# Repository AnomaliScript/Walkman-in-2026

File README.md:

# Walkman-in-2026
As a part of Hack Club's "Fallout" challenge, I attempt to build a replica of Makoto's walkman (from Persona 3) using KiCad, Onshape, and hopes and dreams.

This Walkman composes of many capacitors, resistors, an Audio Jack, a microSD card socket, LCD display, four buttons, an on/off switch, and most importantly, a XIAO-ESP3-S3 to make it all work!
Most, if not all of these components are THT, or "through-hole technology", meaning that the components have pins that go through holes in the PCB, making them easier to soldier, and that's why I chose THT components (with the exceptino of the microSD card reader), because I'm not a soldering expert (yet).

## V0.1
I made my own custom "standoffs" which are supports that support the LCD display, because it needs extra vertical room in order for its pins to be connected to the PCB.  I 3D printed both a "screw" and a "non-screw" version of the standoffs, to test which one would work best (standoffs are small, and the smaller a print is, the worse small details, like screw patterns, will be).

The screw standoff's didn't work, becasue my 3D printer can't print with that amount of sub-millimeter precision, so I'll just have to use the "non-screw" version of the standoffs.

## V0.2
The biggest change from V0.1 was the addition of an Amazon-purchased breakout board that covered both the AudioJack (3.5mm diameter) and PCM5102A stereo.  After all, the PCM5102A is indeed a really tiny chip, and with the soldering iron that I was getting, it wasn't likely that I could've soldered the chip using SMD (surface mount) on my own.  Consequently, I had to rewire the whole PCB (this will happen many times...) to compensate for this change.
What I specifically did was delete the AudioJack and PCM components from the PCB, and put a 16-pin connetor row in its place to set it up for wires to connect to the breakout module (a decision I would later go back on).
I also cleaned up the BOM a little bit, but it still was missing a lot of components compared to the final one (which I will link in the bottom of this README).

I was planning to get many of my components from my school's makerspace, however since Georgia school years end in mid-May, I lost access to those spaces, and therefore couldn't access those resources: this meant that I had to go shop online (i.e. Amazon and Digikey).
V0.2 was also when I finally started to consider how to power this whole contraption, and the conclusion I came up with was simply to add some punches holes (called  "Jumper" in the KiCad schematic) to have the battery wires solder through.

## V0.3
The buttons on the Walkman PCB looks a bit off; maybe it's because they're not tilted 90 degrees!  While implementing right-angle switches, I learned about the different types of drill holes that KiCad offers (I had the wrong type of hole for the switches' footprints which was giving me DRC errors).

This was also when I became very insecure about my power management system, so this was when I learned that the XIAO-ESP3-S3 in fact has a built-in nattery management system that rules out the need for Buck converters and other auxillary power managemtn components, which was a huge relief after having done power research for a couple of days straight.  The only problem was how to get the power tracks/wires to connect to the bottom of the XIAO, becasue that's where the XIAO's battery pads (BATT) are.  Seeing as to how laying the XIAO against teh PCB would make it impossible for a wire to reach under the XIAO, I decided to elevate it using connectors (not shown in the KiCad 3D Viewer below).

## V0.4
I went back on my decision to physically elevate my XIAO from the PCB.
After a family vacation, my refreshed mind preferred to create pads on the XIAO footprint itself.  By adding the BATT pads onto the footprint itself, the XIAO, when it comes in contact with the PCB direcly, would have its BATT pads touch the PCB's corresponding pads, requiring no extraneous equiment to connect the two.
This customization of the orignal XIAO-ESP32-S3 footprint required me to refer to Seeed Studio's offical KiCad files in order to determine the dimensions and position of the BATT pads, becasue the XIAOs that I ordered were still in transit at the time, so I had no other reference.

The XIAO BATT pads and its PCB footprint counterpart, in theory, seemed to perfectly align with each other.

I also learned that I had ordered the wrong type of switch for the power, as I ordered a SW_SPST (a button) instead of a SW_DPST (an actual power switch that toggles), so I had to order SW_DPST switches.
The LCD that I got was also an unexpected (but plesant) surprise: it came with the PCF8574 component (a component that allows for more GPIO pins) already soldered onto the LCD1602.  After realizing that this aligned with my PCB schematic, I gladly deleted the PCF8574 from my schematic and PCB Editor, and more configuration was done.

Due to the unique pin that the LCD came with, however, I had to redo the footprint for the LCD as well.

## V0.5
Reviewing my the PCB, I realized that the 5V pin on the LCD wasn't connected to anything, and thus began the **third** reexamination of my PCB's power management.  After scrutiny, I fixed the 5V pin on the LCD fairly quickly (connect the 5V on the LCD to the VBUS pin on the XIAO), but there was another issue that I found, and it had to do with the BSS138 components.  BSS138s are what are called "bidirectional I2C level shifters", which means they mediate the translation between a higher voltage (e.g. 5V) and a lower voltage (3V).  Cleaning up my schematic to mitigate risks of making errors due to confusion, I then revised the BSS connections.

Once again, I had to rewire everything (BSS138 is a surface-mount/SMD component, which made rerouting a little harder).

I also noticed that I really needed a 3D model for the LCD component, becasue that was not only the biggest part, but it's also one of the most important parts when it came to me designing a housing/case for my PCB.  Surfing through the internet, I landed upon a sketchy-looking 3D model of the exact same component (I copied and pasted the Amazon name of the component into Google), and it was in some Autodesk-specific file format.  After registering for a free trial for Autodesk products (specifically Fusion 360), I converted into an .stl file and imported into OnShape to look at it further.  The model  wasn't that bad, and when I linked the 3D model to my LCD footprint on the PCB in KiCad, it fit right in!
One tiny change had to be made, and it was the deletion of the right-angle pins (I bent the pins on my LCD to make it straight to make it parallel to the PCB surface...I hope that doesn't mess up dimensioning...)

## V1.0
Remember the 16-pin connector that I mentioned?  Their job was to act as pins that wires from the AudioJack breakout module could connect to, but seeing as to how it adds unnecessary space to the Walkman, I designed the AudioJack component as a footprint in the PCB Editor to get rid of the 16-pin connector (this did in fact save a lot of space).  This required some dimensioning, which I did, and I made a rough OnShape model of it.  Exporting it onto the 3D Viewer in my PCB Editor on KiCad, I moved it up a bit (which will represent me using pinn connectors to elevate it) in order to give it some room so it doesn't collide with the right-angle switches.

I utilized my 3D printer to print simplified versions of my PCB to check the footprints and pin dimensions for the XIAO, LCD component, and AudioJack component (not pictured), but after verification I ordered the PCB from JLCPCB, and now I wait for it to come (as well as some other LCSC components).

# BOM (not including delivery fees + tariffs)
| Id      | Name    | Vendor  | Qty     | Cost |
| --- | --- | --- | --- | --- |
| 1 | [microSD card slot](https://www.digikey.com/en/products/detail/molex/0472192001/3044807) | DigiKey | 10 | $14 |
| 2 | [BSS138](https://www.digikey.com/en/products/detail/onsemi/BSS138/244210)| DigiKey | 10 | $2 |
| 3 | [Power Switch (taken from my friend's recommendation)](https://www.lcsc.com/product-detail/Slide-Switches_C-K-OS102011MA1QN1_C226259.html) | LCSC | 10 | $5.25 |
| 4 | [XIAO ESP32S3](https://www.amazon.com/ESP32S3-2-4GHz-Dual-core-Supported-Efficiency-Interface/dp/B0DJ6NQFKX/ref=pd_rhf_dp_s_ci_mcx_mr__d_sccl_1_1/137-7709202-3397348) | Amazon | 3 | $27 |
| 5 | [1602 LCD + PCF 8524 module](https://www.amazon.com/Hosyond-Display-Module-Arduino-Raspberry/dp/B0BWTFN9WF/ref=pd_rhf_dp_s_ci_mcx_mr__d_sccl_1_3/137-7709202-3397348) | Amazon | 3 | $14 |
| 6 | [AudioJack + PCM 5102 module](https://www.amazon.com/PCM5102-PCM5102A-Digital-Converter-Raspberry/dp/B0DNW32Y46/ref=sims_dp_d_dex_ai_rank_model_1_d_v1_d_sccl_1_3/137-7709202-3397348?psc=1) | Amazon | 2 | $9 |
| 7 | [1000mAh LiPo battery](https://www.amazon.com/1000mAh-battery-Rechargeable-Lithium-Connector/dp/B07BTWK13N) | Amazon | 1 | $9 |
| 8 | [Right-Angle Switches](https://www.lcsc.com/product-detail/C49101620.html?spm=wm.ddx.0.xqy___wm.ddl.ddb.0.ddh&lcsc_vid=ElUPAwcDQFlaVF0HQ1dXAwFXFVNbUVFeQFIPBQIHQgQxVlNeR1FZVVVQR1laVTsOAxUeFF5JWBYZEEoKFBINSQcJGk4NBhADEA4cHktSR1RADxALGw%3D%3D) | LCSC | 50 | $0.63 |
| X | X | X | X | ~$81 |

## Additional supplies

I started to get soldering supplies by asking my friend's dad for some, to which he responded with a simple roll of solder and an okay soldering iron.  This worked out fine for the simpler components, but when it came to more complex soldering assemblies such as SMD components, I needed help.
After some discussion with by more-experienced friend, he told me that I needed a pack of liquid/solid flux (just in case if the rosin-core solder didn't have enough), a heatbed for the SMD components, and some solder paste to complement the heatbed for easier soldering for SMD components.
| Id      | Name    | Vendor  | Qty     | Cost |
| --- | --- | --- | --- | --- |
| 1 | [Heatbed](https://www.amazon.com/Soldering-Microcomputer-Technicians-Electronics-Enthusiasts/dp/B0G443BG4X/ref=sr_1_2?sr=8-2) | Amazon | 1 | $27 |
| 2 | [Flux](https://www.amazon.com/SRA-Soldering-Electronics-Lead-Free-Electrical/dp/B008ZIV85A/ref=sr_1_6?crid=3PSC9N7K6VI1P&dib=eyJ2IjoiMSJ9.4lAJRvPbs-mZfOjdNN3yko1QdCRJ7DuF7ITQXP00Zw6-YTXEtz6O56z-3mFeA06DFWn7K46TQMWEEocoB24hUeA2pRWL5PZLodoffU67bT22aAduVxkx_wdd-4mv4hNAZPr-tqz4AYCK0zWmtre61fzN7fRagjiYjk4f0m6PkqVZ_U-DropUBjAUAZUFRuWYf_Zg6Ls1t9Iee1CwaPx7wRCERDrgLYxmO5XsuhNiYI31TFE8GYnA0AEQibicbohzDRZsgtbbjuhwPmBq9184HANk6QaEDnCSlJgSGyVij_4.RXMTRwdvJQXcmnfBtIILk3Vw2HaX5XoBBaaOHqvCQDs&dib_tag=se&keywords=solder+flux&qid=1787439264&sprefix=solder+flu%2Caps%2C151&sr=8-6) | Amazon | 1 | $9 |
| 3 | [Solder Paste](https://www.amazon.com/Particle-Melting-Electronics-Welding-100G/dp/B0FYH9HS2W/ref=sr_1_24?crid=1XXM8RE6MJU3V&dib=eyJ2IjoiMSJ9.RM36QPd0a2H4_bdhGSOKfZJjHoW4TT7FYbYOePXYuUSKFAHb8I43R-8Ku84GS6KqnE81AwtSetvDehl8jUrOpetkE9Lp1e0oAUrra1Ax1yHaP54gxSOjCNy8Qae3zJZ3lqb1vRmu-jv4T_6l-unRR69yQe7E2hoBbOXNDQxANlSyCc-yngeB1UcluzowntyGix_HBKZ0-sbckXMkqIkEe25zazsldICJT3-jejK2Nnjor7P6o3duiNHdLID88EolUzPUfiM_pN3laRQF3XeSDC66AEbr2nc3RMiYHQiKlFM.QaV3XLYiIFU6J7uR8jqXOCL1FU7gVYKlh0sjLuVEvP0&dib_tag=se&keywords=solder+paste&qid=1787439314&sprefix=solder+pas%2Caps%2C222&sr=8-24) | Amazon | 1 | $22 |

After getting these components, I set up shop in my garage, and I opened the garage door so that the yummy lead fumes could escape.  However, I got moved to my back patio after my dad complained after a bunch of bugs came it in from the open garage door.

Finally, after having done most of the soldering to enable theoretical functionality for my Walkman, I tried hooking it up to my computer using a Logi USB-C cable, and after some vibecoding with Claude Opus, I got the Walkman to work...partially.  The display was a little off, and no matter how many times I unplugged and replugged my earbuds, I still couldn't hear anything from the Walkman.  Thankfully, the microSD card reader was working, as well as the LCD after some adjustment, because I saw it displaying the text of the songs that I had loaded onto the microSD card.

Switching out my earbuds for headphones that I usually use, I was finally able to hear the music that was playing!

However, the battery still needed to be implemented into the Walkman PCB, and I soon realized that the V1.0 Walkman PCB wouldn't be able to distribute the LiPo battery's power to all the peripherals on the PCB.  This was because I wired the AudioJack, LCD display, and all the other peripherals other than the microSD card to all use VBUS (5V) power instead of 3.3V power.  The problem lied in how the 3.3V pin, not the VBUS pin, was the only power distributor when the Walkman is disconnected from the XIAO's USB-C's power source.

## V2.0 
With the LiPo power distribution not working and the LCD screen not being entirely accurate to Makoto's Walkman in Persona 3, I returned to the drawing board that is KiCad.  By working with Claude, I found another [LCD screen](https://newhavendisplay.com/2x20-character-lcd-stn-gray-display-with-side-white-backlight-and-pin-header-3v/) online that looked more similar to Makoto's Walkman screen.  Looking at its datasheet, I tried adding it into my Walkman PCB schematic.

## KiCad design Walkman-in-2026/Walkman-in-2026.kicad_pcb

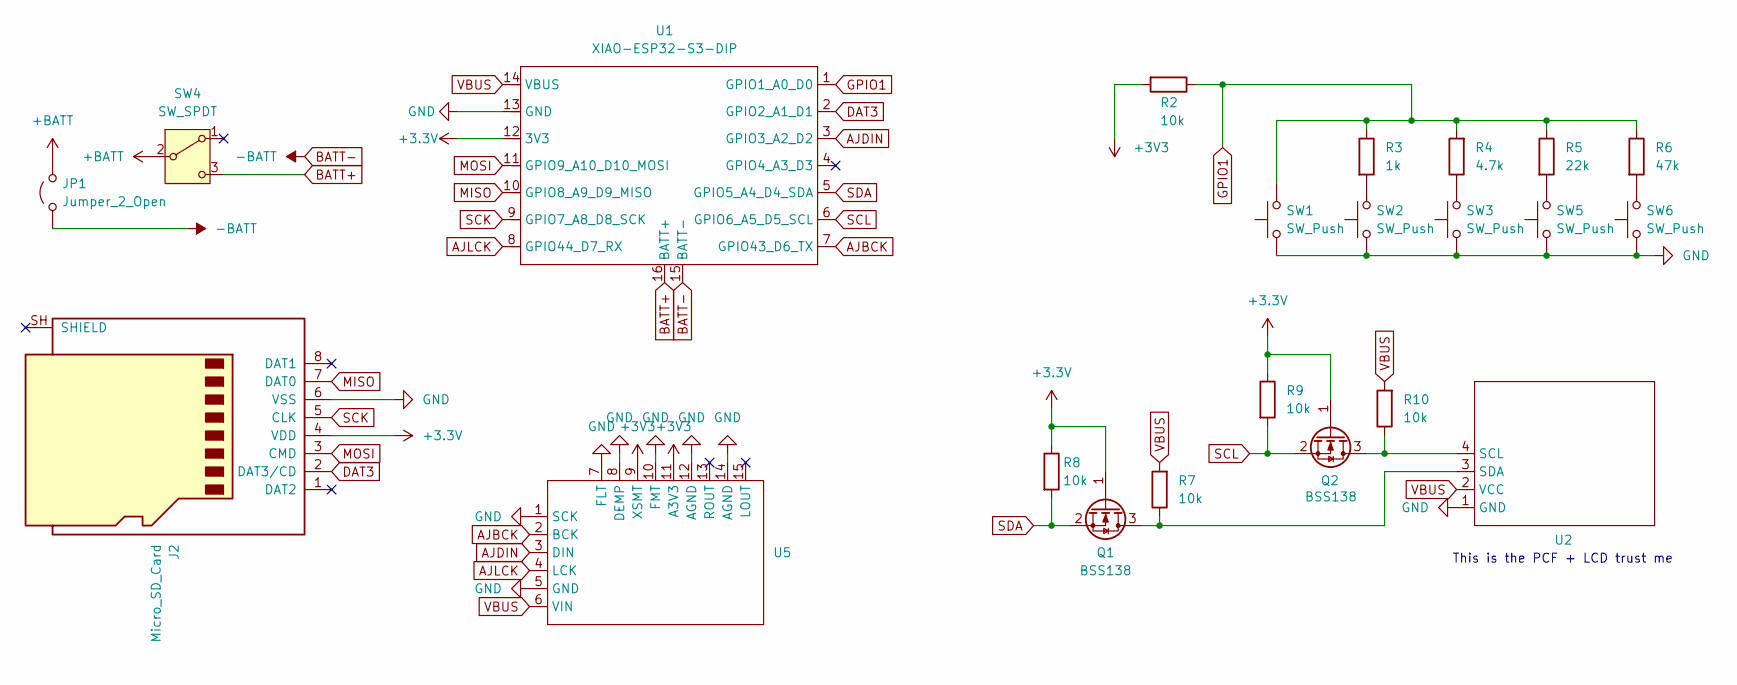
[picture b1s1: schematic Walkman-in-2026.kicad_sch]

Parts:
J2: Micro_SD_Card; microSD_HC_Molex_47219-2001
JP1: Jumper_2_Open; TestPoint_2Pads_Pitch2.54mm_Drill0.8mm
Q1, Q2: BSS138; SOT-23
R2, R7, R8, R9, R10: 10k; R_Axial_DIN0207_L6.3mm_D2.5mm_P7.62mm_Horizontal
R3: 1k; R_Axial_DIN0207_L6.3mm_D2.5mm_P7.62mm_Horizontal
R4: 4.7k; R_Axial_DIN0207_L6.3mm_D2.5mm_P7.62mm_Horizontal
R5: 22k; R_Axial_DIN0207_L6.3mm_D2.5mm_P7.62mm_Horizontal
R6: 47k; R_Axial_DIN0207_L6.3mm_D2.5mm_P7.62mm_Horizontal
SW1, SW2, SW3, SW5, SW6: SW_Push; SW-SMD_TC-S3601-3.5-260G-F0.6
SW4: SW_SPDT; SW_Slide_SPDT_Angled_CK_OS102011MA1Q
U1: XIAO-ESP32-S3-DIP
U2: PCF8574 x LCD1602 combo
U5: PCM x AudioJack Combo

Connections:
+3.3V: J2.4 (VDD), Q1.1 (G), Q2.1 (G), R8.1, R9.1, U1.12 (3V3)
+3V3: R2.2, U5.9 (XSMT), U5.11 (A3V3)
+BATT: JP1.2 (B), SW4.2 (B)
AJBCK: U1.7 (GPIO43_D6_TX), U5.2 (BCK)
AJDIN: U1.3 (GPIO3_A2_D2), U5.3 (DIN)
AJLCK: U1.8 (GPIO44_D7_RX), U5.4 (LCK)
BATT+: SW4.3 (C), U1.16 (BATT+)
BATT-: JP1.1 (A), U1.15 (BATT-)
DAT3: J2.2 (DAT3/CD), U1.2 (GPIO2_A1_D1)
GND: J2.6 (VSS), SW1.1, SW2.1, SW3.1, SW5.1, SW6.1, U1.13 (GND), U2.1 (GND), U5.1 (SCK), U5.5 (GND), U5.7 (FLT), U5.8 (DEMP), U5.10 (FMT), U5.12 (AGND), U5.14 (AGND)
GPIO1: R2.1, R3.1, R4.2, R5.1, R6.1, SW1.2, U1.1 (GPIO1_A0_D0)
MISO: J2.7 (DAT0), U1.10 (GPIO8_A9_D9_MISO)
MOSI: J2.3 (CMD), U1.11 (GPIO9_A10_D10_MOSI)
unnamed: Q1.3 (D), R7.1, U2.3 (SDA)
unnamed: Q2.3 (D), R10.1, U2.4 (SCL)
unnamed: R3.2, SW2.2
unnamed: R4.1, SW3.2
unnamed: R5.2, SW5.2
unnamed: R6.2, SW6.2
SCK: J2.5 (CLK), U1.9 (GPIO7_A8_D8_SCK)
SCL: Q2.2 (S), R9.2, U1.6 (GPIO6_A5_D5_SCL)
SDA: Q1.2 (S), R8.2, U1.5 (GPIO5_A4_D4_SDA)
VBUS: R7.2, R10.2, U1.14 (VBUS), U2.2 (VCC), U5.6 (VIN)

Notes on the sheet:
This is the PCF + LCD trust me

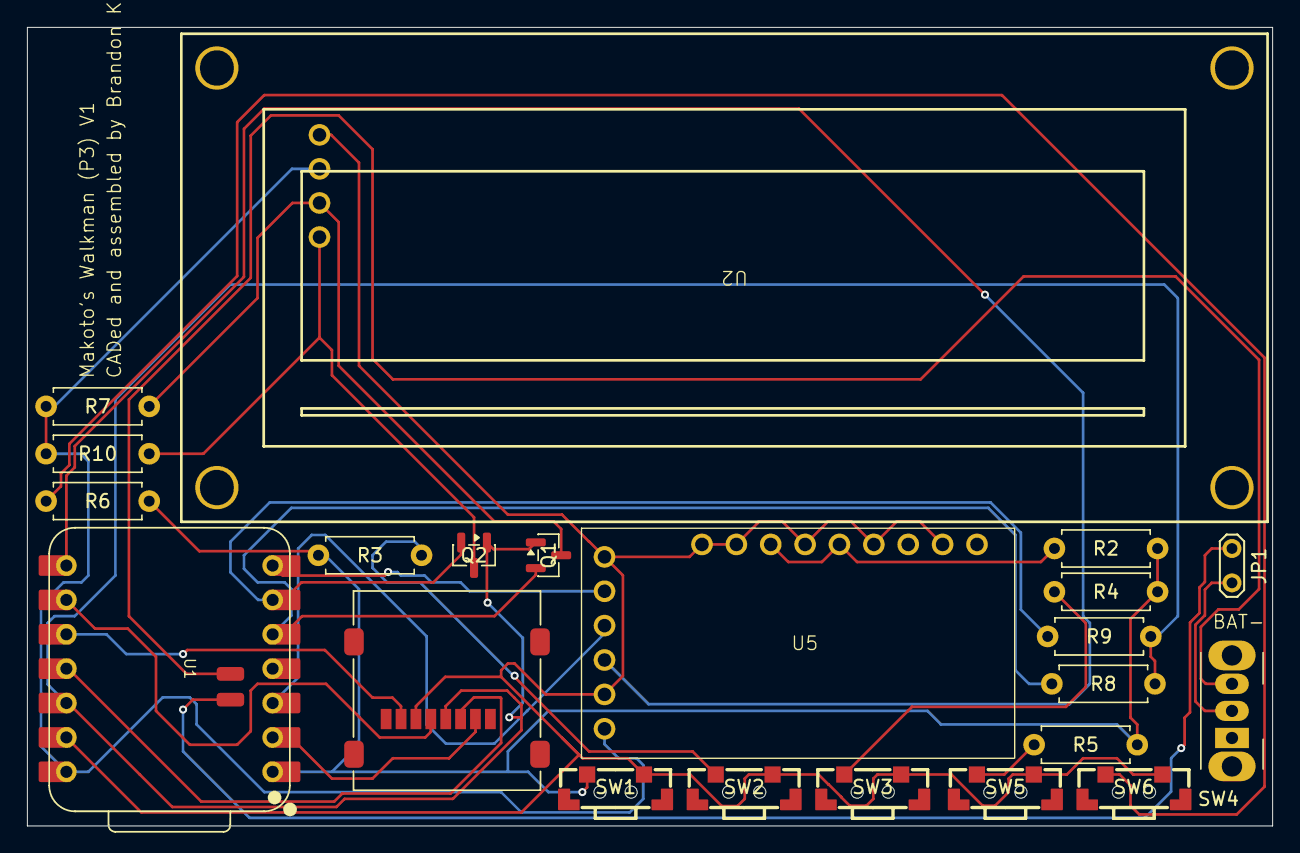
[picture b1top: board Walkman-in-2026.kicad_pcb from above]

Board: 2 copper layers, 92.0 x 59.0 mm, 22 parts (0 on the bottom side), 23 nets.

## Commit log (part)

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2026-04-25 April 24 Session (Rerouting, Audio, Micro SD Card, and Setting Up Capacitors)
2026-04-27 jazz fest working
2026-04-28 moving on to the pcb editor
2026-05-04 May 3rd (end of worlds)
2026-05-07 may 6 session
2026-05-10 Enhance README with project details and rendering info
    Added details about components and 3D rendering for the Walkman project.
2026-05-11 stuff happened ig
2026-05-12 adding a fking stupid battery
2026-05-29 larp
2026-06-15 Adding custom footprints for lcd x pcf and pcm x audiojack
2026-06-22 Revise README with project versioning and details
    Updated project details and clarified component choices.
2026-06-23 v1 final
2026-06-24 Document version history and component updates in README
    Added detailed version history from V0.1 to V1.0, including changes to PCB design, components, and assembly notes.
2026-06-24 Update README with version history and project details
    Expanded version history and detailed changes for each iteration of the project, including component modifications and PCB adjustments.
